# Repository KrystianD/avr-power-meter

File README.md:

avr-power-meter
======

Device for monitoring bidirectional DC energy usage using various shunt resistors. Designed to mount directly on the shunt.

This version targets 48 V systems (supports up to 85 V on the sensing side).

It is galvanically isolated from the power supply to prevent ground loops.

It communicates via the Modbus RTU protocol over an RS-485 interface.

The core components are the `INA228` sensor and an `ATtiny1626` microcontroller.

### History

See the v1 (test) version in [[v1]](https://github.com/KrystianD/avr-power-meter/tree/v1) branch. \
See the v2 (for 24V systems) version in [[v2]](https://github.com/KrystianD/avr-power-meter/tree/v2) branch.

# Board

<br/>

# Photos

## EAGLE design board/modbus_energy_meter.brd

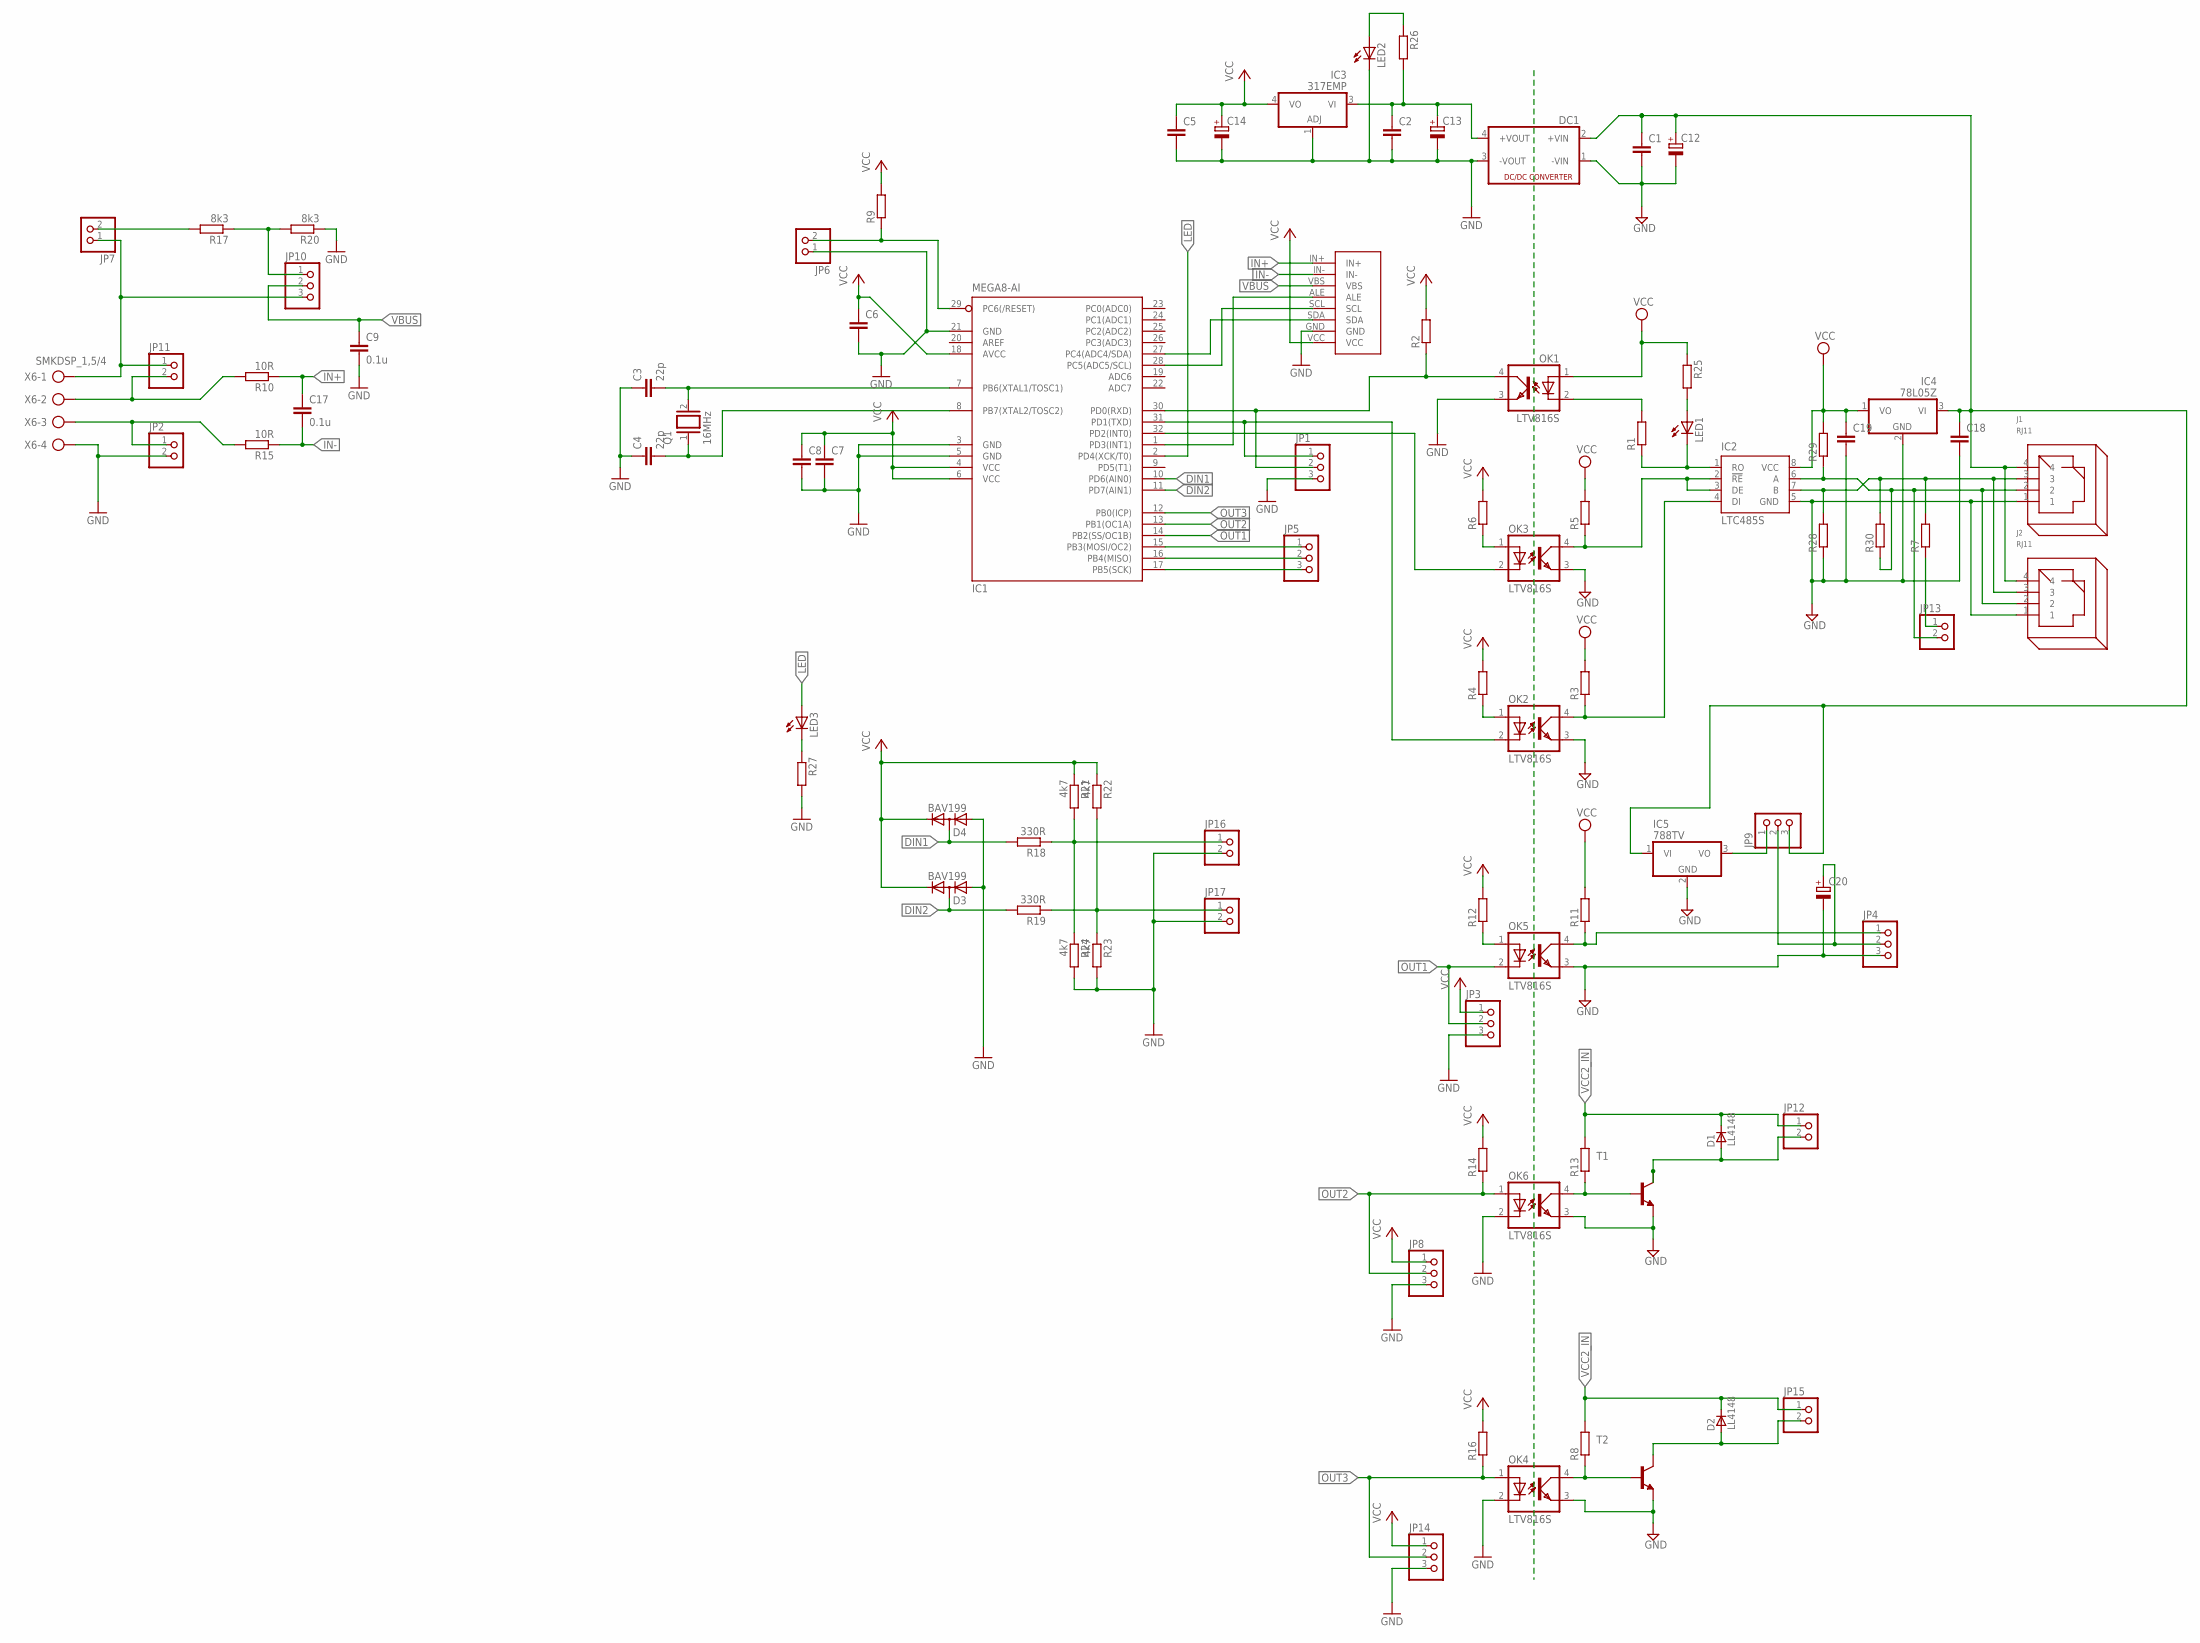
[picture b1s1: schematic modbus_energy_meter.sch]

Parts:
C1, C2, C5, C6, C7, C8, C18, C19: C-EUC0805; C0805
C3, C4: 22p; C0805
C9, C17: 0.1u; C0805
C12: CPOL-EUE2.5-6; E2,5-6
C13, C14, C20: CPOL-EUE2.5-5; E2,5-5
D1, D2: LL4148; SOD80_DO213AA_MINIMELF
D3, D4: BAV199; SOT23
DC1: NME
IC1: MEGA8-AI; TQFP32-08
IC2: LTC485S; SOIC8
IC3: 317EMP; SOT223
IC4: 78L05Z; TO92
IC5: 788TV; TO220V
J1, J2: RJ11
JP1, JP3, JP4, JP5, JP8, JP9, JP10, JP14: PINHD-1X3; 1X03
JP2, JP6, JP7, JP11, JP12, JP13, JP15, JP16, JP17: PINHD-1X2; 1X02
LED1, LED2, LED3: LEDCHIPLED_0805; CHIPLED_0805
OK1, OK2, OK3, OK4, OK5, OK6: LTV816S; SMD4
Q1: 16MHz; QS
R1, R6, R28, R29: R-EU_R1206; R1206
R2, R3, R4, R5, R7, R8, R9, R11, R12, R13, R14, R16, R25, R26, R27, R30: R-EU_R0805; R0805
R10, R15: 10R; R0805
R17, R20: 8k3; R0805
R18, R19: 330R; R0805
R21, R22, R23, R24: 4k7; R0805
T1, T2: BC818-NPN-SOT23-BEC; SOT23-BEC
U$1: INA226MODULE
X6: SMKDSP_1,5/4

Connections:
A: IC2.6 (A), J1.2, J2.2, JP13.2, R29.1, R30.1
B: IC2.7 (B), J1.3, J2.3, R7.2, R28.2, R30.2
DI: IC2.4 (DI), OK2.4 (COL), R3.1
DIN1: D4.3 (AC), IC1.10 (PD6(AIN0)), R18.2
DIN2: D3.3 (AC), IC1.11 (PD7(AIN1)), R19.2
DIR: IC2.2 (!RE), IC2.3 (DE), OK3.4 (COL), R5.1
DIR_CTRL: IC1.32 (PD2(INT0)), OK3.2 (C)
DI_CTRL: IC1.31 (PD1(TXD)), JP1.1, OK2.2 (C)
GND: C2.2, C3.1, C4.1, C5.2, C6.2, C7.2, C8.2, C9.2, C13.-, C14.-, D3.1 (A), D4.1 (A), DC1.3 (-VOUT), IC1.3 (GND), IC1.5 (GND), IC1.21 (GND), IC3.1 (ADJ), JP1.3, JP2.2, JP3.3, JP6.1, JP8.3, JP14.3, JP16.2, JP17.2, LED2.C, OK1.3 (EMIT), OK4.2 (C), OK6.2 (C), R20.1, R23.2, R24.2, R27.2, U$1.GND, X6.4
GND2: C1.2, C12.-, C18.2, C19.2, C20.-, DC1.1 (-VIN), IC2.5 (GND), IC4.2 (GND), IC5.2 (GND), J1.1, J2.1, JP4.3, OK2.3 (EMIT), OK3.3 (EMIT), OK4.3 (EMIT), OK5.3 (EMIT), OK6.3 (EMIT), R28.1, T1.E, T2.E
IN+: C17.1, R10.1, U$1.IN+
IN+_IN: JP11.2, R10.2, X6.2
IN-: C17.2, R15.1, U$1.IN-
IN-_IN: JP2.1, R15.2, X6.3
LED: IC1.2 (PD4(XCK/T0)), LED3.A
unnamed: IC1.1 (PD3(INT1)), U$1.ALE
unnamed: C3.2, IC1.7 (PB6(XTAL1/TOSC1)), Q1.2
unnamed: JP13.1, R7.1
unnamed: JP17.1, R19.1, R22.2, R23.1
unnamed: OK4.4 (COL), R8.1, T2.B
unnamed: C4.2, IC1.8 (PB7(XTAL2/TOSC2)), Q1.1
unnamed: D2.A, JP15.2, T2.C
unnamed: OK1.2 (C), R1.2
unnamed: IC1.15 (PB3(MOSI/OC2)), JP5.1
unnamed: JP16.1, R18.1, R21.2, R24.1
unnamed: LED3.C, R27.1
unnamed: OK2.1 (A), R4.1
unnamed: OK3.1 (A), R6.1
unnamed: LED2.A, R26.1
unnamed: IC1.16 (PB4(MISO)), JP5.2
unnamed: IC1.17 (PB5(SCK)), JP5.3
unnamed: LED1.A, R25.2
unnamed: D1.A, JP12.2, T1.C
unnamed: OK5.1 (A), R12.1
unnamed: OK6.4 (COL), R13.1, T1.B
unnamed: JP7.2, R17.2
OUT1: IC1.14 (PB2(SS/OC1B)), JP3.2, OK5.2 (C)
OUT1_SIGNAL: JP4.1, OK5.4 (COL), R11.1
OUT1_VCC: C20.+, JP4.2, JP9.2
OUT1_VCC_STAB: IC5.3 (VO), JP9.1
OUT2: IC1.13 (PB1(OC1A)), JP8.2, OK6.1 (A), R14.1
OUT3: IC1.12 (PB0(ICP)), JP14.2, OK4.1 (A), R16.1
RO: IC2.1 (RO), LED1.C, R1.1
RO_CTRL: IC1.30 (PD0(RXD)), JP1.2, OK1.4 (COL), R2.1
RST: IC1.29 (PC6(/RESET)), JP6.2, R9.1
SCL: IC1.28 (PC5(ADC5/SCL)), U$1.SCL
SDA: IC1.27 (PC4(ADC4/SDA)), U$1.SDA
VBUS: C9.1, JP10.2, U$1.VBS
VBUS_DIVIDED: JP10.1, R17.1, R20.2
VBUS_IN: JP7.1, JP10.3, JP11.1, X6.1
VCC: C5.1, C6.1, C7.1, C8.1, C14.+, D3.2 (C), D4.2 (C), IC1.4 (VCC), IC1.6 (VCC), IC1.18 (AVCC), IC3.4 (VO), JP3.1, JP8.1, JP14.1, R2.2, R4.2, R6.2, R9.2, R12.2, R14.2, R16.2, R21.1, R22.1, U$1.VCC
VCC2: C19.1, IC2.8 (VCC), IC4.1 (VO), OK1.1 (A), R3.2, R5.2, R11.2, R25.1, R29.2
VCC2_IN: C1.1, C12.+, C18.1, D1.C, D2.C, DC1.2 (+VIN), IC4.3 (VI), IC5.1 (VI), J1.4, J2.4, JP9.3, JP12.1, JP15.1, R8.2, R13.2
VCC5V: C2.1, C13.+, DC1.4 (+VOUT), IC3.3 (VI), R26.2

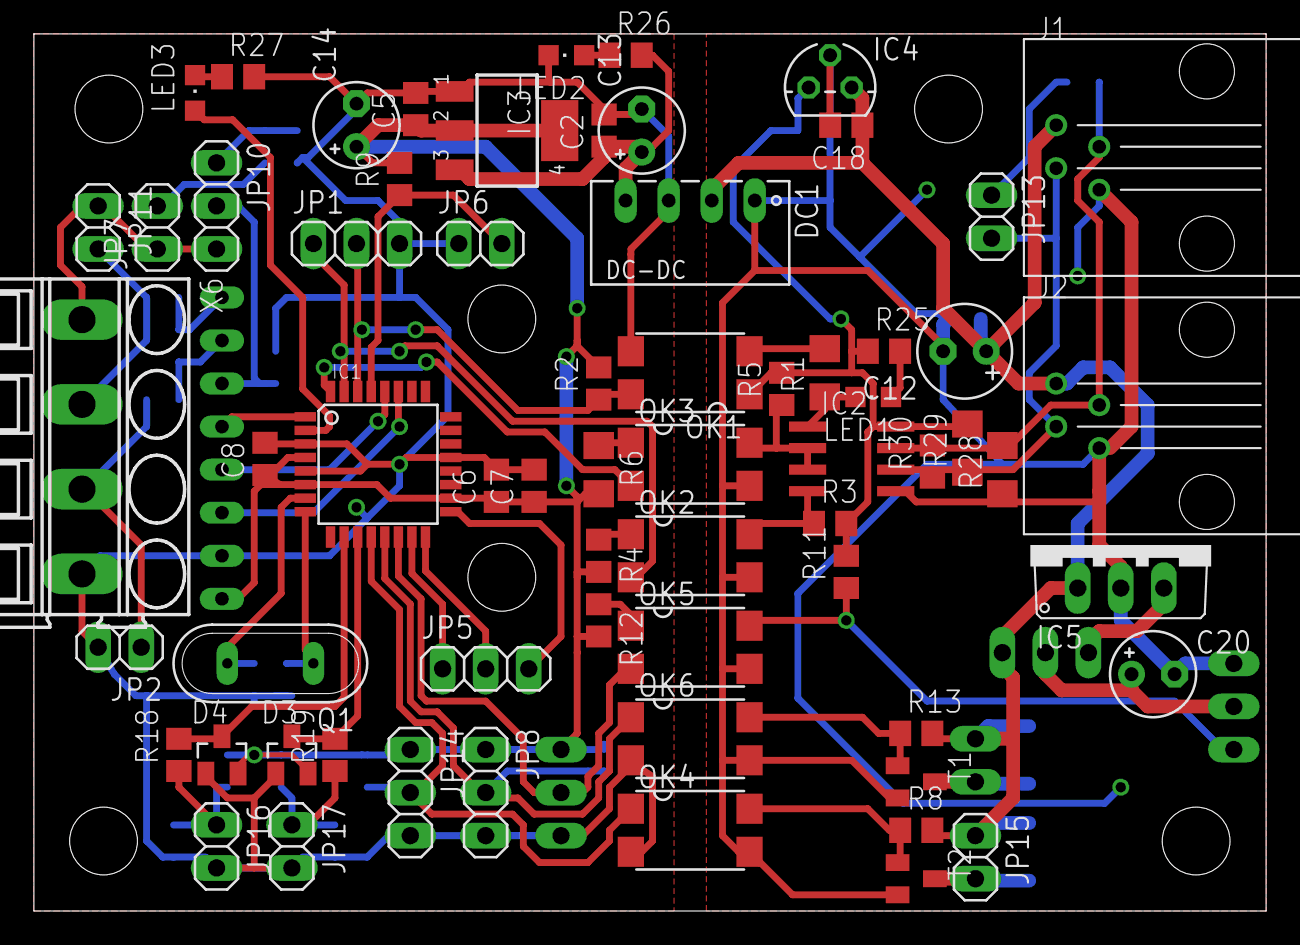
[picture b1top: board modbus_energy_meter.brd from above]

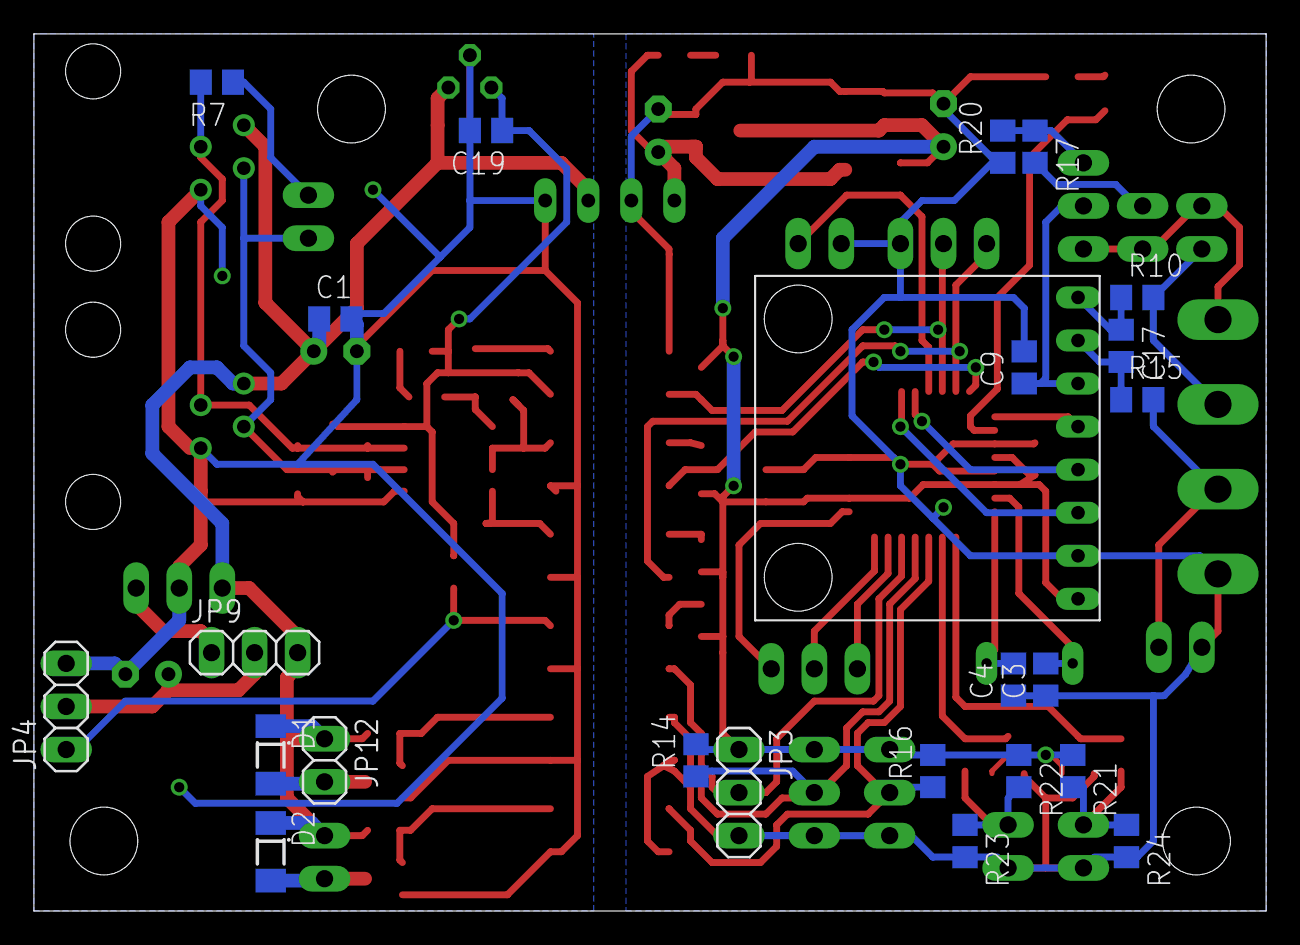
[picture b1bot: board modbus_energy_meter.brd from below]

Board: 2 copper layers, 72.7 x 51.7 mm, 89 parts (24 on the bottom side), 54 nets.

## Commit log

2025-10-29 minor schematic updates
2026-06-28 register name fix
2026-06-28 updated ksystem
2026-06-28 board update
2026-06-28 reboot asynchronously to properly send modbus ack
2026-06-28 disabled stdio for production
2026-06-28 exposed mcu voltage as a modbus register
2026-06-28 updated dev_attiny
